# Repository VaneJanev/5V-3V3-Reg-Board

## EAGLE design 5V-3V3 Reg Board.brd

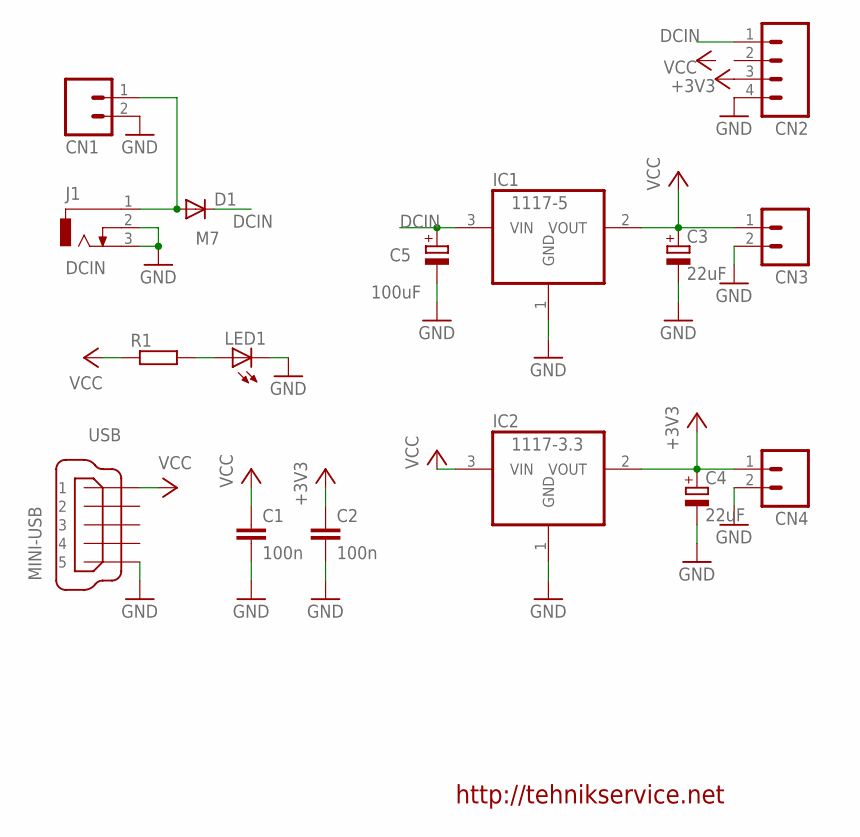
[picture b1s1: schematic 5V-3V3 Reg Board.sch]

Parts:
C1, C2: 100n; C0805
C3, C4: 22uF; E2,5-5
C5: 100uF; E2,5-5
CN1, CN3, CN4: M02; 02P
CN2: M04; 04P
D1: M7; DO-214AC
IC1: 1117-5; SOT223
IC2: 1117-3.3; SOT223
J1: DCIN; DCJ0202
LED1: LEDCHIPLED_0805; CHIPLED_0805
R1: R-EU_R0805; R0805
USB: MINI-USB; 32005-201

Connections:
+3V3: C2.1, C4.+, CN2.3, CN4.1, IC2.2 (VOUT)
DCIN: C5.+, CN2.1, D1.C, IC1.3 (VIN)
GND: C1.2, C2.2, C3.-, C4.-, C5.-, CN1.2, CN2.4, CN3.2, CN4.2, IC1.1 (GND), IC2.1 (GND), J1.2, J1.3, LED1.C, USB.5
unnamed: LED1.A, R1.2
unnamed: CN1.1, D1.A, J1.1
VCC: C1.1, C3.+, CN3.1, IC1.2 (VOUT), IC2.3 (VIN), R1.1, USB.1

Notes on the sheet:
http://tehnikservice.net

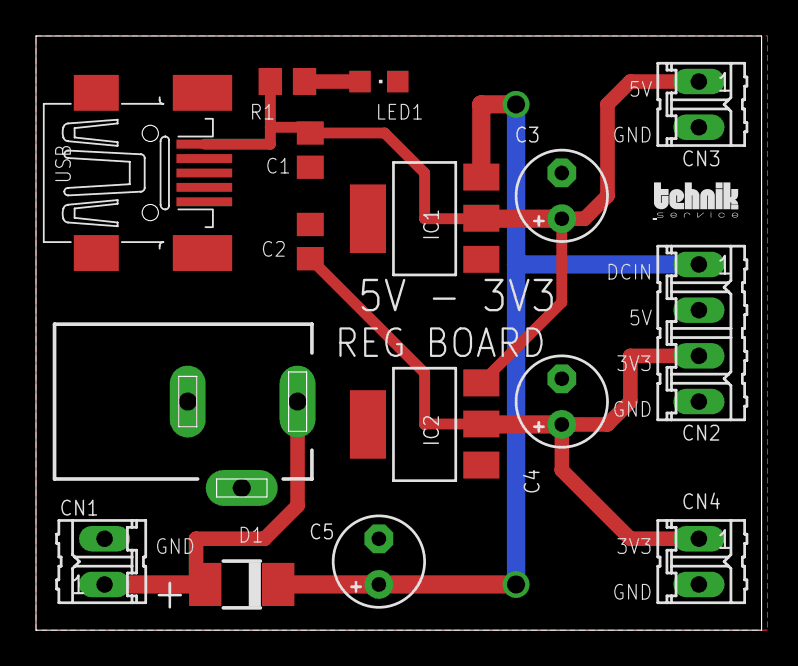
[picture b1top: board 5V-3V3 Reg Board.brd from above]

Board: 2 copper layers, 40.3 x 33.0 mm, 17 parts (0 on the bottom side), 6 nets.

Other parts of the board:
E$1: LOGOT

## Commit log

2015-06-03 :neckbeard: Added .gitattributes
2015-06-03 5V-3V3-Reg-Board
    Eagle Design
